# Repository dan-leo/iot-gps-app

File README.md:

# iot-gps-app
IoT app/widget that periodically captures GPS coordinates and streams to a backend for storage and display on a map.

## Objectives

The objectives of the project are to demonstrate the following:

* Solve a problem with very little information available
* Ability to pick up basic technical skills fast
* Quickly determine relevant technical tools to use.

## Project description

* Write a software program for a mobile device that will capture the Longitude & Latitude GPS coordinates at 1 second intervals. (Any mobile platform is acceptable i.e., IOS, Android, React Native, Flutter)
* Take this stream of data and push it to a backend service where it is saved.
* Create a widget on the backend service to display the GPS data on a map.

## Pointers

*  ThingsBoard as a backend solution.

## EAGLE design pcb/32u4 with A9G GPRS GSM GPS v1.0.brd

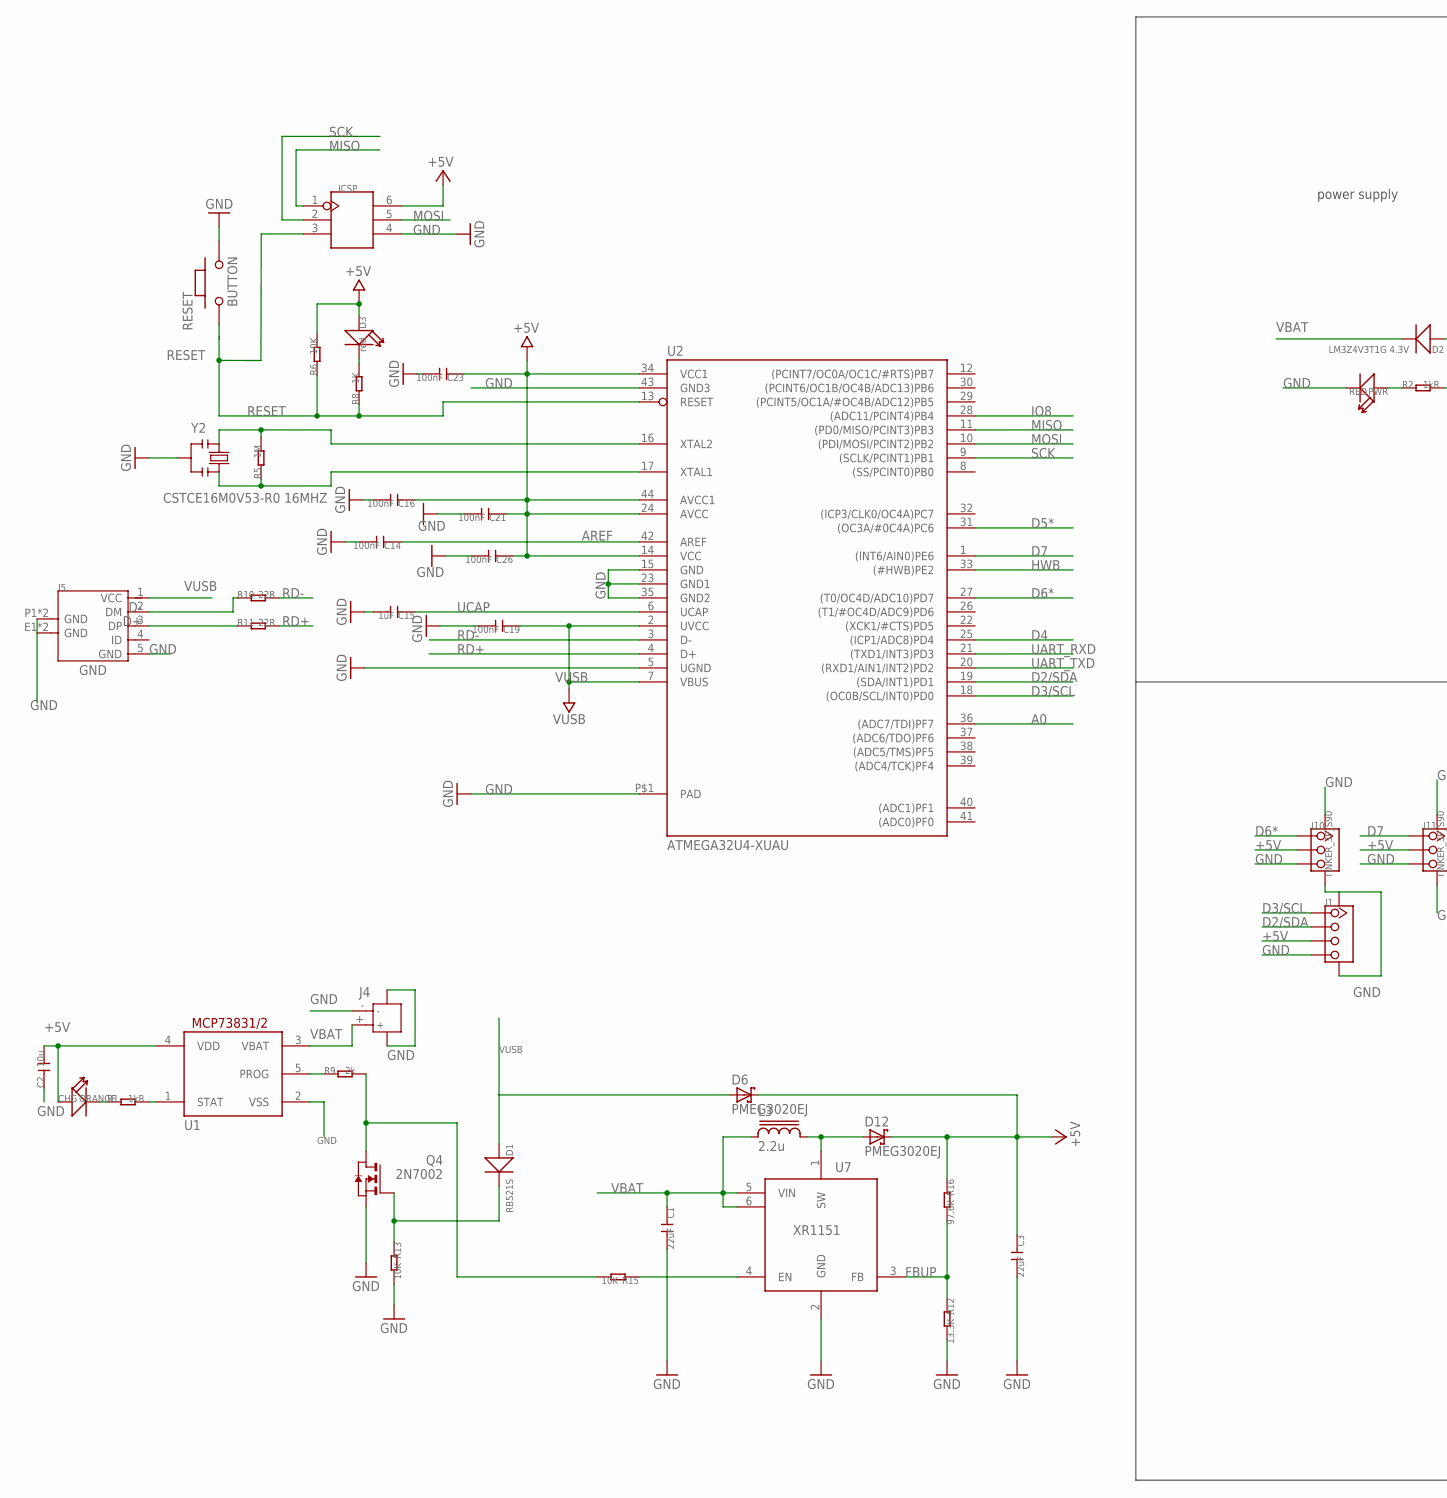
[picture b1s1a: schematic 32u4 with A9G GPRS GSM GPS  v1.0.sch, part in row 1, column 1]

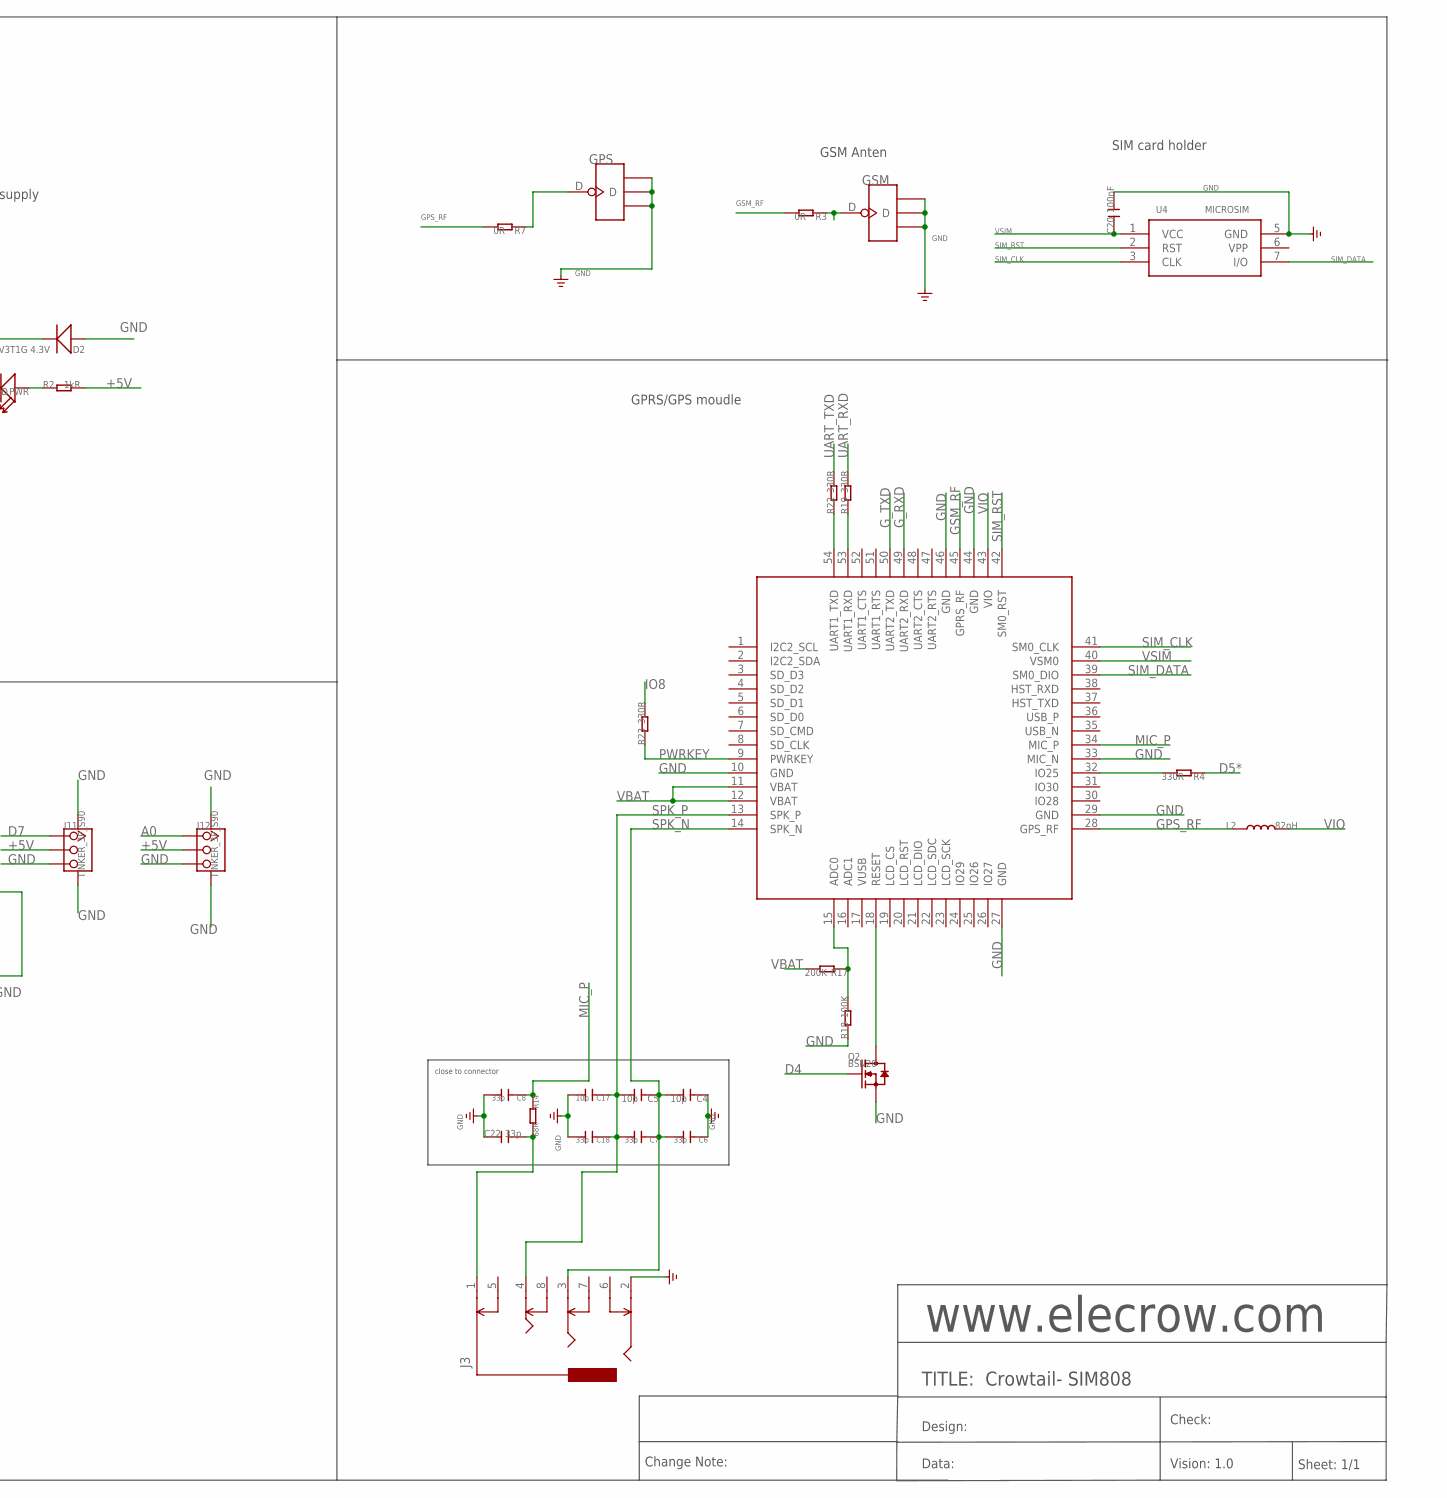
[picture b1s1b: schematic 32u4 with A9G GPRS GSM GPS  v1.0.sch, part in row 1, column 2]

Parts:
C1, C3: 22uF; C0603
C2: 10u; C0603
C4, C5, C17: 10p; C0402
C6, C7, C18: 33p; C0402
C8, C22: 33p; C0603
C14, C16, C19, C20, C21, C23, C26: 100nF; C0603
C15: 1uF; C0603
CHG: ORANGE; D0603
D1: RB521S; SOD523
D2: LM3Z4V3T1G 4.3V; SOD323
D3: red; LED-0603
D6, D12: PMEG3020EJ; SOD-323
GPS: ANTENNA-U-FL; 4P-U-FL
GSM: ANTENNA-U-FL; 4P-U-FL
ICSP: HEADER-2X3P-2.0; 2X3P-2.0
J1: TWIG-4P-2.0-SMD-FEMALE-REINFORCE'90D'; 4P-SMD-2.0-90D
J3: AUDIO-8P'PJ-3536-L6S'; 8P-3.5-SMD
J4: JACK-JST-2P-SMD-PW'2.0'; JST-SMD-2.0-90D
J5: MICRO-USB-5P-340015001; B-SMD-5P
J10, J11, J12: TINKER_3P_S90
L2: 82nH; L0603
L3: 2.2u; CD32
PWR: RED; D0603
Q2: BSN20; SOT23@1
Q4: 2N7002; SOT23
R1, R2: 1kR; R0603
R3, R7: 0R; R0603
R4, R19, R22, R23: 330R; R0603
R5: 1M; R0603
R6, R13, R15: 10K; R0603
R8: 1K; R0603
R9: 2k; R0603
R10, R11: 22R; R0603
R12: 13.3K; R0603
R14: 68R; R0603
R16: 97.6K; R0603
R17: 200K; R0603
R18: 100K; R0603
RESET: BUTTON; 157SW
U1: MCP73831/OT; SOT23-5L
U2: ATMEGA32U4-XUAU; TQFP44-PAD
U4: MICROSIM
U5: A9G
U7: XR1151; SOT23-6L
Y2: CSTCE16M0V53-R0 16MHZ; RESONATOR

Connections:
+5V: C2.2, C3.1, C16.1, C21.1, C23.1, C26.1, CHG.+, D3.+, D6.C, D12.C, ICSP.6, J1.3, J10.2, J11.2, J12.2, R2.2, R6.2, R16.1, U1.4 (VDD), U2.14 (VCC), U2.24 (AVCC), U2.34 (VCC1), U2.44 (AVCC1)
A0: J12.1, U2.36 ((ADC7/TDI)PF7)
AREF: C14.1, U2.42 (AREF)
D2/SDA: J1.2, U2.19 ((SDA/INT1)PD1)
D3/SCL: J1.1, U2.18 ((OC0B/SCL/INT0)PD0)
D4: Q2.1 (G), U2.25 ((ICP1/ADC8)PD4)
D5*: R4.1, U2.31 ((OC3A/#0C4A)PC6)
D6*: J10.1, U2.27 ((T0/OC4D/ADC10)PD7)
D7: J11.1, U2.1 ((INT6/AIN0)PE6)
D+: J5.3 (DP), R11.1
D-: J5.2 (DM), R10.1
FBUP: R12.1, R16.2, U7.3 (FB)
GND: C1.2, C2.1, C3.2, C4.1, C6.1, C8.2, C14.2, C15.2, C16.2, C17.2, C18.2, C19.2, C20.2, C21.2, C22.1, C23.2, C26.2, D2.+, GPS.GND1, GPS.GND2, GPS.GND3, GSM.GND1, GSM.GND2, GSM.GND3, ICSP.4, J1.4, J1.SS1, J1.SS2, J3.2, J4.3, J4.4, J4.- (2), J5.5 (GND), J5.E1 (GND), J5.E2 (GND), J5.P1 (GND), J5.P2 (GND), J10.3, J10.SS1, J10.SS2, J11.3, J11.SS1, J11.SS2, J12.3, J12.SS1, J12.SS2, PWR.-, Q2.2 (S), Q4.2 (S), R12.2, R13.2, R18.1, RESET.2, U1.2 (VSS), U2.5 (UGND), U2.15 (GND), U2.23 (GND1), U2.35 (GND2), U2.43 (GND3), U2.P$1 (PAD), U4.5 (GND), U5.10 (GND), U5.27 (GND), U5.29 (GND), U5.33 (MIC_N), U5.44 (GND), U5.46 (GND), U7.2 (GND), Y2.2
GPIO2: R4.2, U5.32 (IO25)
GPS_RF: L2.1, R7.2, U5.28 (GPS_RF)
GSM_RF: R3.2, U5.45 (GPRS_RF)
G_RXD: U5.49 (UART2_RXD)
G_TXD: U5.50 (UART2_TXD)
HWB: U2.33 ((#HWB)PE2)
IO8: R23.2, U2.28 ((ADC11/PCINT4)PB4)
MIC_P: C8.1, R14.1, U5.34 (MIC_P)
MISO: ICSP.1, U2.11 ((PD0/MISO/PCINT3)PB3)
MOSI: ICSP.5, U2.10 ((PDI/MOSI/PCINT2)PB2)
unnamed: D12.A, L3.2, U7.1 (SW)
unnamed: Q4.3 (D), R9.2, R15.2
unnamed: D1.-, Q4.1 (G), R13.1
unnamed: R17.1, R18.2, U5.15 (ADC0)
unnamed: GSM.D, R3.1
unnamed: PWR.+, R2.1
unnamed: GPS.D, R7.1
unnamed: Q2.3 (D), U5.18 (RESET)
unnamed: R19.1, U5.53 (UART1_RXD)
unnamed: R15.1, U7.4 (EN)
unnamed: CHG.-, R1.1
unnamed: R22.1, U5.54 (UART1_TXD)
unnamed: D3.-, R8.2
unnamed: R1.2, U1.1 (STAT)
unnamed: C22.2, J3.1, R14.2
unnamed: R9.1, U1.5 (PROG)
PWRKEY: R23.1, U5.9 (PWRKEY)
RD+: R11.2, U2.4 (D+)
RD-: R10.2, U2.3 (D-)
RESET: ICSP.3, R6.1, R8.1, RESET.1, U2.13 (RESET)
SCK: ICSP.2, U2.9 ((SCLK/PCINT1)PB1)
SIM_CLK: U4.3 (CLK), U5.41 (SM0_CLK)
SIM_DATA: U4.7 (I/O), U5.39 (SM0_DIO)
SIM_RST: U4.2 (RST), U5.42 (SM0_RST)
SPK_N: C4.2, C5.1, C6.2, C7.1, J3.3, U5.14 (SPK_N)
SPK_P: C5.2, C7.2, C17.1, C18.1, J3.4, U5.13 (SPK_P)
UART_RXD: R19.2, U2.21 ((TXD1/INT3)PD3)
UART_TXD: R22.2, U2.20 ((RXD1/AIN1/INT2)PD2)
UCAP: C15.1, U2.6 (UCAP)
VBAT: C1.1, D2.-, J4.+ (1), L3.1, R17.2, U1.3 (VBAT), U5.11 (VBAT), U5.12 (VBAT), U7.5 (VIN), U7.6 (VIN1)
VIO: L2.2, U5.43 (VIO)
VSIM: C20.1, U4.1 (VCC), U5.40 (VSM0)
VUSB: C19.1, D1.+, D6.A, J5.1 (VCC), U2.2 (UVCC), U2.7 (VBUS)
XTAL3: R5.2, U2.16 (XTAL2), Y2.1
XTAL4: R5.1, U2.17 (XTAL1), Y2.3

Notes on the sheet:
TITLE: Crowtail- SIM808
www.elecrow.com
Design:
Check:
Data:
Vision: 1.0
Sheet: 1/1
power supply
SIM card holder
Change Note:
GSM Anten
GPRS/GPS moudle
close to connector

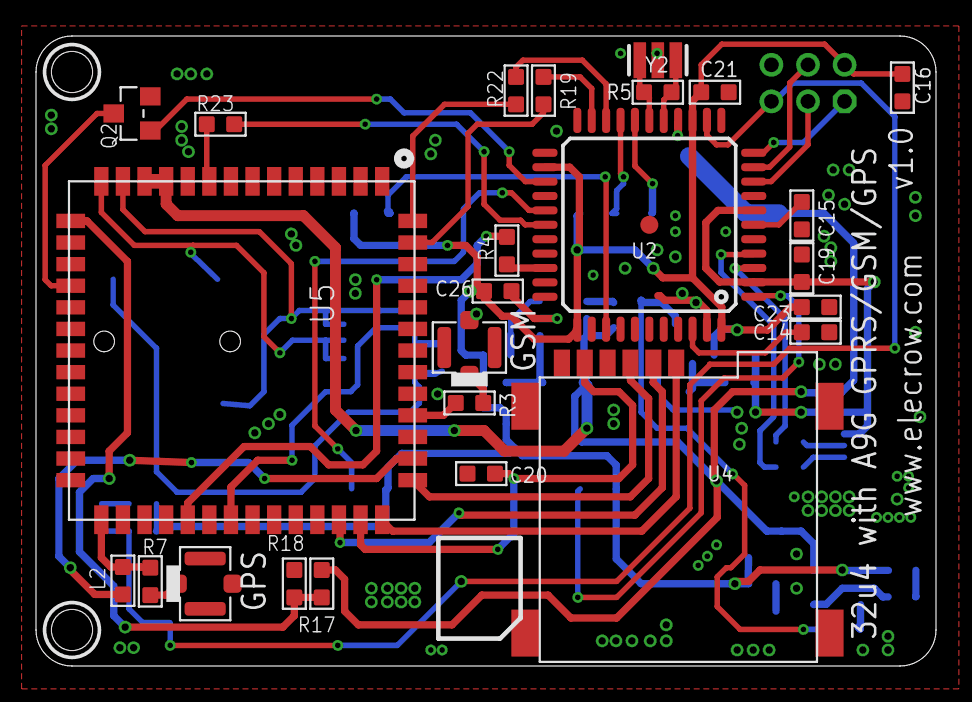
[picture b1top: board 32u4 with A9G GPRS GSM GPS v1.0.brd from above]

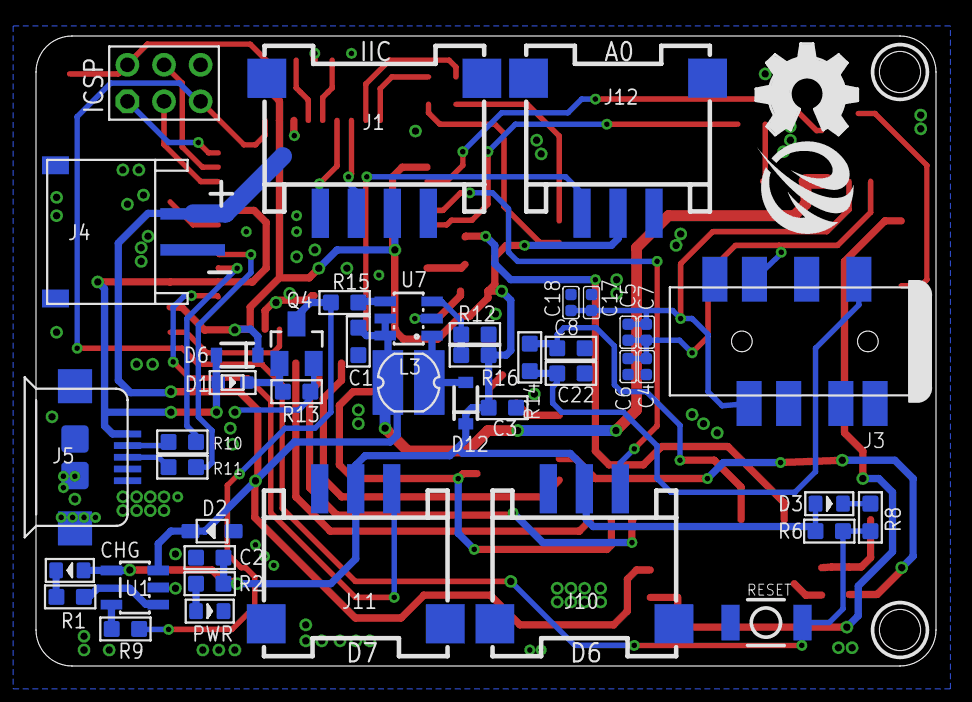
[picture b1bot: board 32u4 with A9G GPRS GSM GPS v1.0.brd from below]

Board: 2 copper layers, 50.0 x 35.0 mm, 70 parts (45 on the bottom side), 55 nets.

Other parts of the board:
LOGO2: LOGO-OSHW-FILLX0200-NT; OSHW_FILLX200_NOTEXT
U$1: ELECROW-NEW

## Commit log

2020-06-11 get current location
2020-06-11 task scheduled every second
2020-06-12 periodic lat-long updates to thingsboard.io backend
2020-06-12 cleanup
2020-06-12 apk release
2020-06-16 added pcb
